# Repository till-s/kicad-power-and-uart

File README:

Fork of power-test-1 with reference numbers starting at 1000.
Helps importing into other projects.

Note: re-annotating schematic from kicad and re-importing into pcbnew
works!!! So it is easy to change the base to something else...

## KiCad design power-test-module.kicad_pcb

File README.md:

# USBC Power and UART Module

A small module (~40mmx25mm) powered by USB-C which provides
a 3.3V/3A power-converter and a UART.

# Features
 - detects available power of upstream port
 - jumper to select 1.5A or 3A capability (the power-supply
   remains OFF if the upstream port does not provide enough
   current).
 - LED indicates insufficient upstream power.
 - FT232 UART
 - (Optional) additional legacy mini-USB connector can
   be jumpered to provide USB data. The idea is that you
   can use a (permanent) USB-C power supply (wall-wart) and 
   use the legacy connector, e.g., for a temporary debugging
   session.
     - power always from USB-C
     - data either from USB-C or legacy as selected by jumper

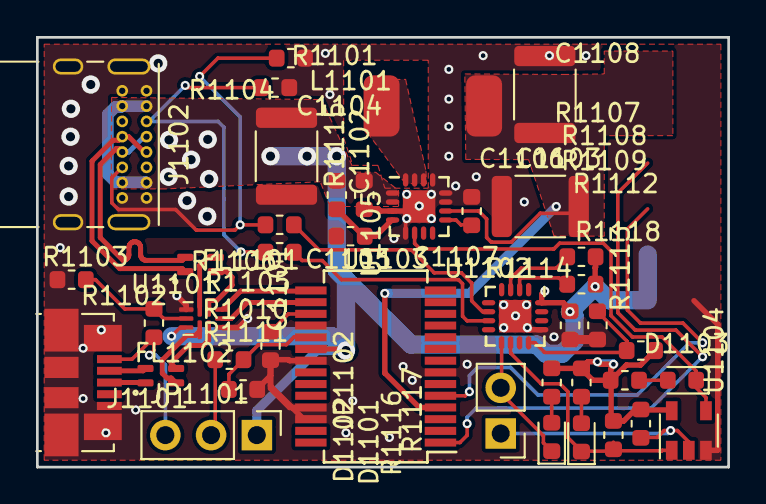
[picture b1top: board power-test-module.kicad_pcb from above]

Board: 2 copper layers, 38.4 x 23.9 mm, 41 parts (0 on the bottom side), 35 nets.

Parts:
C1101, C1102, C1103, C1105, C1107: 100nF_603; C_0603_1608Metric
C1104, C1106, C1108: 22uF_lo_ESR; C_1812_4532Metric
D1101, D1102, D1103: LED; LED_0603_1608Metric
FL1101, FL1102: EMI_Filter_LL_14; WE_CNSW
J1101: USB_miniB; USB_Micro-B_Molex_47346-0001
J1102: USB_C_Receptacle_USB2.0; USB_C_Receptacle_GCT_USB4085_smaller_holes
JP1101: Jumper_3_Bridged12; PinHeader_1x03_P2.54mm_Vertical
JP1102: Jumper_NO_Small; PinHeader_1x02_P2.54mm_Vertical
L1101: 1uH; L_CDMC6D28
R1010, R1101, R1104, R1109: 5k1; R_0603_1608Metric
R1102, R1103, R1116, R1117: R100k; R_0603_1608Metric
R1105, R1106, R1107, R1108, R1111: R10k; R_0603_1608Metric
R1112: 35k7; R_0603_1608Metric
R1113, R1114, R1118: 1k5; R_0603_1608Metric
R1115: 1; R_0603_1608Metric
U1101: USB3740B-AI9; UQFN-10_1.6x2.1mm_P0.5mm
U1102: UTC2000; QFN-16-1EP_3x3mm_P0.5mm_EP1.8x1.8mm
U1103: FT232RL; SSOP-28_5.3x10.2mm_P0.65mm
U1104: 74LVC1G00; SOT-23-5
U1105: SC185; QFN-16-1EP_3x3mm_P0.5mm_EP1.8x1.8mm

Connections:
+3V3_PWR_OUT: C1106.1, C1108.1, L1101.1, U1103.4, U1105.10
+5V_PWR_OUT: C1102.1, C1103.2, C1104.1, J1102.A4, J1102.A9, J1102.B4, J1102.B9, JP1101.1, R1107.1, R1108.1, R1112.1, R1113.1, R1114.1, R1115.2, R1116.1, R1117.1, R1118.1, U1101.5, U1102.16, U1103.20, U1104.5, U1105.1, U1105.2
/Sheet5C4CE702/USB1_N: FL1101.2, U1101.1
/Sheet5C4CE702/USB1_P: FL1101.3, U1101.2
/Sheet5C4CE702/USB2_N: FL1102.3, U1101.7
/Sheet5C4CE702/USB2_P: FL1102.2, U1101.6
/Sheet5C4CE702/USB_B_N: FL1102.4, J1101.2
/Sheet5C4CE702/USB_B_P: FL1102.1, J1101.3
/Sheet5C4CE702/USB_C_D_N: FL1101.1, J1102.A7, J1102.B7
/Sheet5C4CE702/USB_C_D_P: FL1101.4, J1102.A6, J1102.B6
/Sheet5C4CE702/USB_N: U1101.9, U1103.16
/Sheet5C4CE702/USB_P: U1101.10, U1103.15
GND: C1101.2, C1102.2, C1103.1, C1104.2, C1105.2, C1106.2, C1107.2, C1108.2, J1101.5, J1101.6, J1102.A1, J1102.A12, J1102.B1, J1102.B12, J1102.S1, R1101.2, R1103.1, R1104.2, R1109.2, R1111.2, U1101.3, U1101.8, U1102.13, U1102.17, U1103.7, U1103.18, U1103.21, U1103.25, U1103.26, U1104.3, U1105.3, U1105.5, U1105.11, U1105.12, U1105.13, U1105.17
unnamed: C1101.1, U1103.17
unnamed: C1105.1, R1115.1, U1105.4
unnamed: C1107.1, U1105.9
unnamed: D1101.1, R1116.2, U1102.10, U1104.1
unnamed: D1101.2, R1113.2
unnamed: D1102.1, JP1102.2, U1102.9
unnamed: D1102.2, R1114.2
unnamed: D1103.1, U1104.4, U1105.6
unnamed: D1103.2, R1118.2
unnamed: J1101.1, JP1101.3, R1102.2
unnamed: J1102.A5, R1104.1, R1105.1
unnamed: J1102.B5, R1101.1, R1106.1
unnamed: JP1101.2, R1010.1
unnamed: JP1102.1, R1117.2, U1104.2
unnamed: L1101.2, U1105.14, U1105.15, U1105.16
unnamed: R1010.2, R1111.1, U1103.19
unnamed: R1102.1, R1103.2, U1101.4
unnamed: R1105.2, U1102.7
unnamed: R1106.2, U1102.6
unnamed: R1107.2, U1102.3
unnamed: R1108.2, U1102.2
unnamed: R1109.1, R1112.2, U1102.12

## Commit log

2021-06-23 git import of power-test-1
2021-06-23 added rescue.lib to git
2021-06-23 renaming power-test-1 -> power-test-module (step 1, renaming files)
2021-06-23 added 'xxx-cache.lib' to git
2021-06-23 renamed power-test-1 -> power-test-module in resp. files
2021-06-23 added rescue.dcm to git
2021-06-23 sym-lib-table: fixed path to trigbox.lib
2021-06-23 updated library symbols (usb-c, usb-otg, ft232)
2021-06-23 replaced VIN_3V3 with original symbol from trigbox.lib
2021-06-23 Revert "replaced VIN_3V3 with original symbol from trigbox.lib"
    This reverts commit 9420d5290e32625fca25a5553c309d02b920cb52.
2021-06-23 replaced VIN3V3 with original from trigbox.lib
2021-06-23 replaced resistor symbols with originals from trigbox.lib
2021-06-23 replaced all rescued symbols by originals from trigbox.lib; removed rescue.lib
2021-06-23 fixed design-rule issues
    - removed stray via
    - replaced 2 single-row headers by a 2x6 (vertical) header to
    avoid court-yard overlaps.
2021-06-23 re-annotated with base number 1000
2021-06-23 use hierarchical labels from power-and-uart sheet
2021-06-23 use QFN-16 footprint from proj-library
2021-06-28 swapped USBC connector; jlcpcb hole distance.
    - use usbc-usb2.0 variant with more power pins
    - enforce .5mm hole spacing (jlcpcb)
2021-06-28 use special +5/+3V3 labels with more specific net names
    This allows easier integration since these are global labels
    and using more specific names helps avoiding clashes.
    The labels are stored in the 'rescue' library.
    Strangely: the same trick did not work for GND. Kicad always
    insists the net name remains 'GND' (it does work, however if
    a new schematic is created - then the different net name for
2021-06-28 removed global labels for UART-TX/RX
    There referred to MIO pins on the CPU board which don't really
    belong here; also: avoid global labels for a module.
2021-06-28 replaced PMOD connector by hierarchical sheet labels; removed power flags
2021-06-28 re-annotated for merging; updated PCB
2021-06-28 reannotated top-level board
    (annotations go into sub-sheets)
2021-07-01 added README.md
2021-07-06 sheet numbers were updated as lan9254 module was added
2021-07-07 various mods to adapt to dev-board
2021-07-07 added part numbers for EMI filter + LEDs;
    Also changed reset pullup from 4k7 to 5k1 (for sake of fewer different values)
2021-07-07 added/updated part number of inductor
2021-07-07 more part numbers
2021-07-08 PCB: fixed USB4085 footprint; has wrong slits
2021-07-08 changed some net-classes to avoid conflicts with base-board
2021-07-09 changed inductor to TDK part (availability)
2021-07-20 don't recall changes...
